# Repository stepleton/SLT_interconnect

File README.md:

# SLT card system wire-to-board interconnect

This project aims to construct a modern replacement for the wire-to-board
connectors that IBM used inside some products incorporating their proprietary
Solid Logic Technology (SLT) and Monolithic System Technology (MST) circuit
design systems. The design has features like wide circuit board traces intended
to make it suitable for use as a power connector, but there's no reason it
couldn't be used for logic interconnect as well.

## Fair warning

This hardware design and all other materials distributed alongside it are made
available for free with NO WARRANTY OF ANY KIND. Any system that interfaces
with hardware built from this design could suffer malfunction, data loss,
physical damage, or other harms. Some of these effects could be permanent
and/or unrepairable. If you're not prepared to risk these consequences, don't
use these resources.

## Background and motivation

Most people familiar with SLT and MST will think of the square aluminium
housings for hybrid circuits and ICs (respectively) that appeared on IBM
components from the 1960s through the 1990s. As it happens, SLT and MST
specifications also described ways of building circuit boards and connecting
them together. SLT and MST-based components saw widespread use in IBM products,
from typewriters to large mainframe computers.

SLT and MST's most common methods of interconnect were based on 24-pin
header-style connectors. "Plugs" (my terminology) were simply made from two
rows of twelve individual metal pins embedded in a circuit board; these were
usually found on boards meant to connect other boards together, like
backplanes. "Sockets" that mated with these plugs were formed from metal
spring contacts lined up on the edges of circuit boards and surrounded by a
plastic shroud; these were usually found on modular cards that held electronic
components (ICs, resistors, etc.). They could also appear on wire-to-board
connectors, where multiple wires or a flat ribbon cable would be soldered
directly to a small circuit board with an integrated socket connector on one
edge.

[This blog post](http://techandtrouble.blogspot.com/2014/04/happy-50th-system360-pt5-anatomy-of-slt.html)
presents a good illustrated overview of SLT and MST cards and their connectors.
As it notes, the unusual arrangement of 1/8-inch (3.175mm) spacing between pins
on the same row, plus the 1/4-inch (6.35mm) spacing between rows, is
incompatible with common header connectors manufactured today.

Lacking off-the-shelf options for SLT and MST interconnect, we can arrange
modern components in a way that is compatible with the IBM designs.

## Gallery and notes

![Socket and plug adaptors lying on their sides, connectors facing the viewer
](pics/adaptors_flat.jpg)

_Figure 1._ Our wire-to-board adaptor is economically constructed from two
small circuit boards joined together perpendicularly, and from single-pin
header pins and sockets arranged according to the 1/8-inch (3.175mm) and
1/4-inch (6.35mm) spacing requirements.

![Socket and plug adaptors standing on their connectors
](pics/adaptors_upright.jpg)

_Figure 2._ The two circuit boards are "glued" together by solder joints that
also connect the connector header pins and sockets to the plated through-holes
where wires will terminate. Threading the wires through an oval-shaped hole on
the vertical circuit board can help them stay tidy and may offer some amount of
strain relief. The mechanical strength of the solder-bonded joint between the
circuit boards is considerable, and most applications are unlikely to require
additional reinforcement there.

![Close-up of the connector end of the socket adaptor](
pics/connector_socket.jpg)

_Figure 3._ The nonstandard pin spacing makes it a bit tricky to ensure a tidy
alignment of the constituent pins and sockets, especially if these parts are
made by trimming breakaway or cuttable strips and therefore vary in size.
Perfection may be impossible, but persistence can give you a functional
arrangement that orients square pins and square sockets to align roughly with
the board itself. Note that like the plastic shroud on the original IBM socket
connector, the connector's horizontal circuit board is also polarised by square
notches in two of its corners.

_Figure 4._ The plug adaptor can mate with an original IBM SLT/MST socket, like
the one on this wire-to-board power connector from an IBM 5100 portable
computer. It's not clear that this arrangement would be reliable without an
additional means of securing the connectors together: by wiggling both of them
around the connection as if it were a hinge, they can come apart fairly easily.

_Figure 5._ Naturally, the plug and socket adaptors can connect to each other,
but the same caveat about security applies.

![The socket adaptor installed in the location where the IBM 5100's power
supply connector goes](pics/restraint_5100_1.jpg)

_Figure 6._ When made with low-profile pin sockets, the socket adaptor can fit
into the same places where real IBM wire-to-board socket adaptors go. Like the
IBM original, our adaptor is liable to come loose of the plug unless it is
restrained somehow. For this, the IBM 5100 makes use of a metal bracket coated
in a non-conductive black enamel finish.

![A close-up of the bracket impinging on some of the socket adaptor's exposed
solder joints](pics/restraint_5100_2.jpg)

_Figure 7._ Unfortunately, there is a problem. A restraining device like this
metal bracket may impinge on the exposed solder joints that attach the
individual header pin sockets to the horizontal circuit board. If the device is
conductive or if it has a non-conductive coating that can wear away, these pins
may be shorted.  The designs of modern pin header sockets and of the original
IBM plug connector make it unlikely that a different circuit board design can
avoid this issue.

![A close-up of wear on the edge of the bracket that presses down on the
adaptor](pics/bracket_wear.jpg)

_Figure 8._ This close-up of the IBM 5100's bracket suggests that its enamel
coating is already wearing away. The best option for avoiding shorts in
situations like these may be to add additional layers of insulation between the
adaptor and the restraint. One specific option in this setting could be to
apply a durable lacquer or varnish to the solder joints, and then to supplement
the bracket's enamel coating with a folded strip of polyimide ("Kapton") tape.

## Parts

Our adaptors require shorter "low profile" components in order to fit in the
same places where the original IBM plugs and sockets were designed to go.

For socket adaptors, the header pin sockets should extend no further than 5.2mm
from the horizontal circuit board. So far, the components used have been
[Samtec CES-101-01-S-S](https://www.samtec.com/products/ces-101-01-s-s)
single-pin sockets, though socket adaptors made with these may be more liable
to "back out" from original IBM plugs than the IBM sockets were. Note that
using even shorter pin-header sockets than these might cause the adaptor to
rest too low in the plug for the original restraint to keep it in place.

For plug adaptors, the header pins should probably not have a mating contact
length that extends beyond 5mm. So far, the components used have been
single-pin 3M 951101-8622-AR pins (no convenient link).

## Assembly

The design files in this repository describe a single "combined" circuit board
with two detachable pieces. The image above shows both sides of this combined
board. Its lower detachable portion forms the "horizontal" circuit board while
the upper portion forms the "vertical" circuit board.

Both sides of the vertical circuit board are functionally identical. The
horizontal circuit board is different: it has one side with bare metal
"fingers" that reach in towards its centre (bottom right in the image).

1. **Detach the vertical and horizontal circuit boards** and the two small
   connecting stubs across all perforations. Throw the stubs away. Using
   sandpaper, a file, an emery board, or some other abrasive tool, file down
   any remnants of the stub that protrude from the edges of the circuit boards.

2. **Plug the tabs of the vertical circuit board into the holes in the
   horizontal circuit board**, making certain that the bare fingers on the
   horizontal circuit board are next to the exposed metal traces on the
   vertical circuit board. Trace the connections from the horizontal board
   pins/sockets to the vertical board plated through holes to make sure the
   arrangement suits your needs; if not, flip the vertical board over.

3. Temporarily secure both boards so that they are as close to perpendicular
   as possible, then **solder the vertical board to the horizontal board** by
   making angled solder bridges between each horizontal board finger and its
   nearest vertical board exposed trace.

4. **Install pin-header pins or sockets** so that they extend from the
   horizontal board on the side opposite the vertical board. This is the
   trickiest part of assembly as both pins and sockets can wiggle around a lot.
   It may be marginally easier if you are assembling one plug adaptor and one
   socket adaptor simultaneously. Try plugging your pins and sockets into each
   other, then sandwiching them between two horizontal boards to create an
   arrangement similar to [figure 5 above](#gallery-and-notes). Naturally you
   will want all of the pins to be attached to one horizontal board and all of
   the sockets to be attached to the other.

   You will need to pinch both connectors together until you have a few of the
   pins and sockets tacked into place with solder. From there, as you solder
   the rest of the pins and sockets in place, it may be useful to use a pair of
   tweezers to rotate and reposition the pin/socket pairs so that they are
   lined up as neatly as possible. 

5. **Tidy the pins and sockets**. Reflowing each pin or socket solder joint and
   manually aligning the pins or sockets can help arrange them even more
   neatly. An additional tactic available to people making a plug adaptor and
   a socket adaptor at the same time is to plug the adaptors into each other
   with various misalignments and offsets, then reflow mated pin and socket
   joints individually in hopes that pins and sockets will change position
   slightly to accommodate the positions of their nonstandard counterparts.
   With a few iterations of this a more regular average positioning might be
   achieved, but your mileage may vary.

## Other notes

To the fullest extent possible, this design is released into the public domain.
Nobody owns it.

## Acknowledgements

Thanks as usual are owed to the [bitsavers.org](http://bitsavers.org) archive
of technical documentation.

## Revision history

22 August 2021: Initial release 
(Tom Stepleton, [stepleton@gmail.com](mailto:stepleton@gmail.com), London)

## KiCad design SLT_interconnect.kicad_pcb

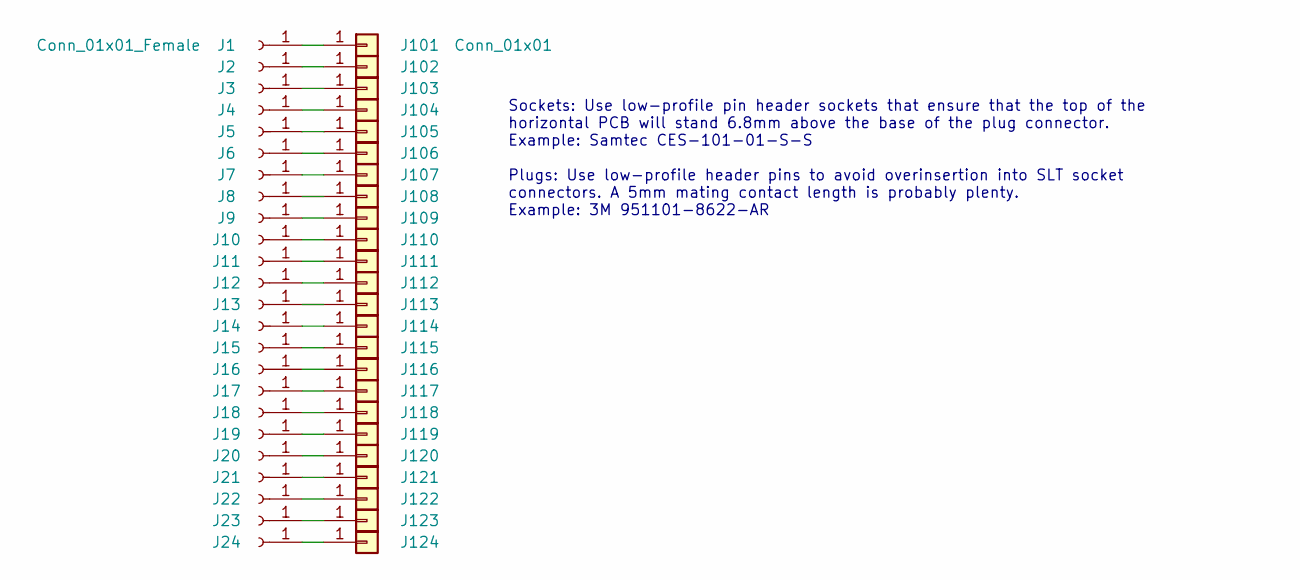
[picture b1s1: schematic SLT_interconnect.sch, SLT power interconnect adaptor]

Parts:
J1, J2, J3, J4, J5, J6, J7, J8, J9, J10, J11, J12, J13, J14, J15, J16, J17, J18, J19, J20, J21, J22, J23, J24: Conn_01x01_Female; PinSocket_1x01_P2.54mm_Vertical
J101, J102, J103, J104, J105, J106, J107, J108, J109, J110, J111, J112, J113, J114, J115, J116, J117, J118, J119, J120, J121, J122, J123, J124: Conn_01x01; SolderWire-0.25sqmm_1x01_D0.65mm_OD1.7mm

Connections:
unnamed: J1.1, J101.1
unnamed: J10.1, J110.1
unnamed: J11.1, J111.1
unnamed: J2.1, J102.1
unnamed: J3.1, J103.1
unnamed: J4.1, J104.1
unnamed: J5.1, J105.1
unnamed: J6.1, J106.1
unnamed: J7.1, J107.1
unnamed: J8.1, J108.1
unnamed: J9.1, J109.1
unnamed: J12.1, J112.1
unnamed: J13.1, J113.1
unnamed: J14.1, J114.1
unnamed: J15.1, J115.1
unnamed: J16.1, J116.1
unnamed: J17.1, J117.1
unnamed: J18.1, J118.1
unnamed: J19.1, J119.1
unnamed: J20.1, J120.1
unnamed: J21.1, J121.1
unnamed: J22.1, J122.1
unnamed: J23.1, J123.1
unnamed: J24.1, J124.1

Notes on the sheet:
Sockets: Use low-profile pin header sockets that ensure that the top of the horizontal PCB will stand 6.8mm above the base of the plug connector. Example: Samtec CES-101-01-S-S Plugs: Use low-profile header pins to avoid overinsertion into SLT socket connectors. A 5mm mating contact length is proba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

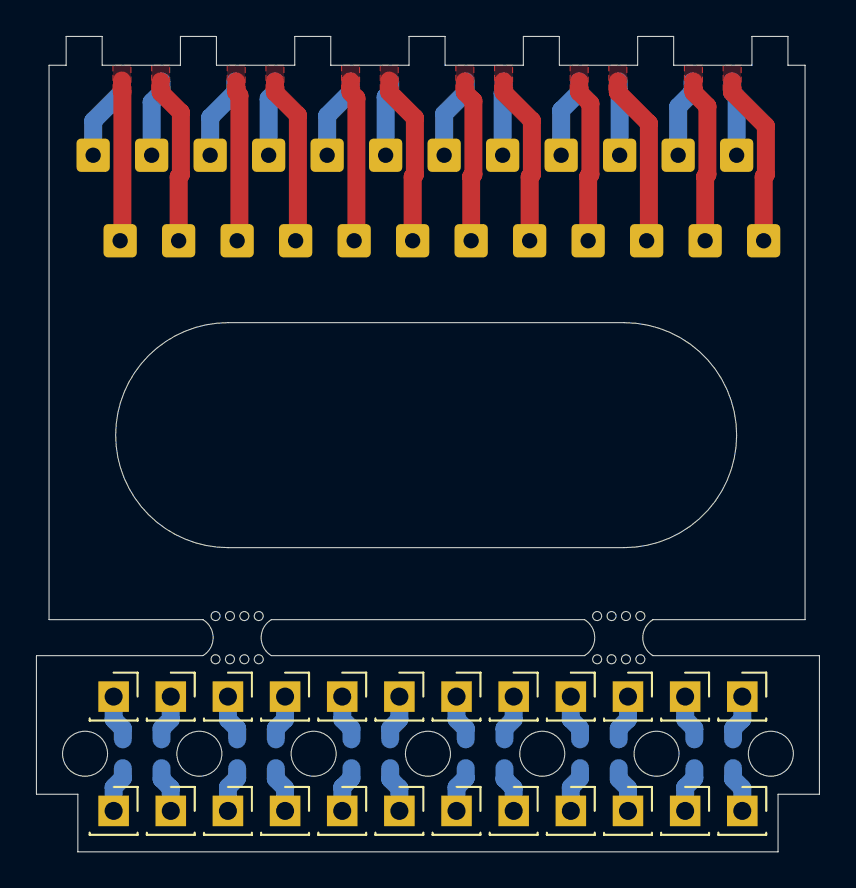
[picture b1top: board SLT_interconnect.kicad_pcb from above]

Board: 2 copper layers, 43.5 x 45.3 mm, 48 parts (0 on the bottom side), 24 nets.

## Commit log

2021-08-22 Add readme and images.
2021-08-22 Minor readme edits
2021-08-22 Fix picture paths in README.md
2021-08-22 Add Gerbers and kicad files

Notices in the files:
SLT_interconnect.kicad_pcb:
Forfeited into the public domain with NO WARRANTY
